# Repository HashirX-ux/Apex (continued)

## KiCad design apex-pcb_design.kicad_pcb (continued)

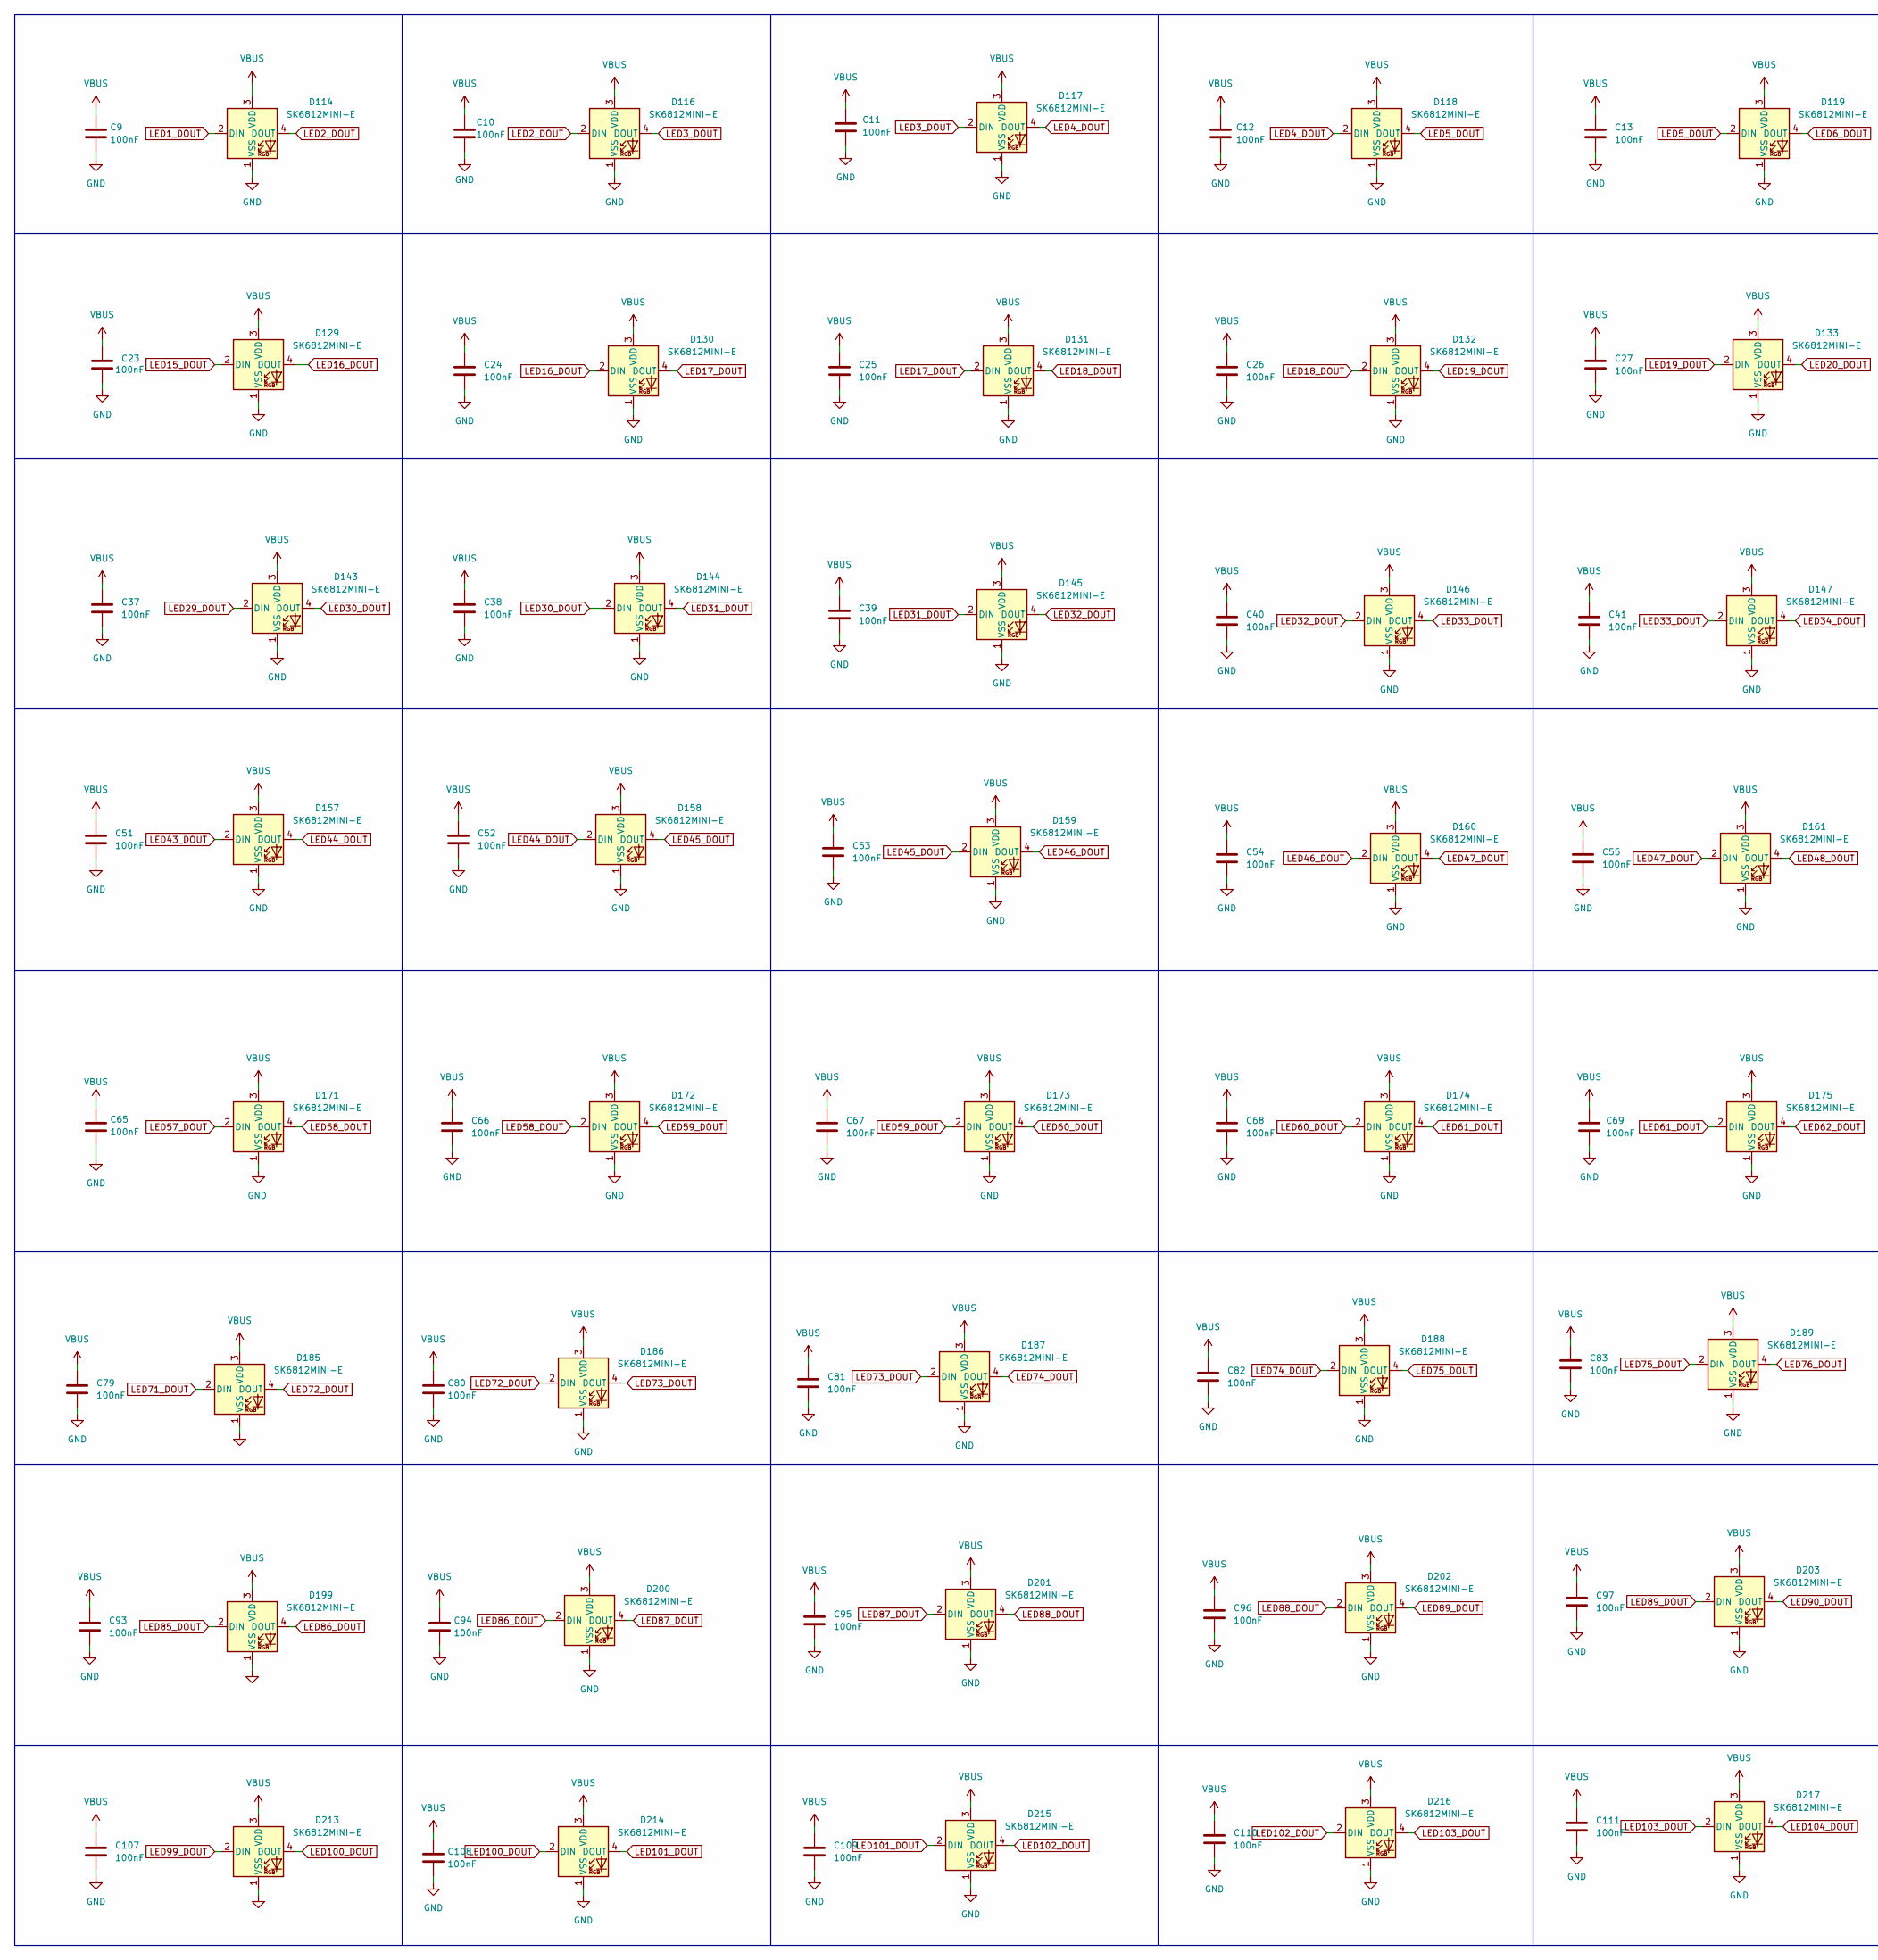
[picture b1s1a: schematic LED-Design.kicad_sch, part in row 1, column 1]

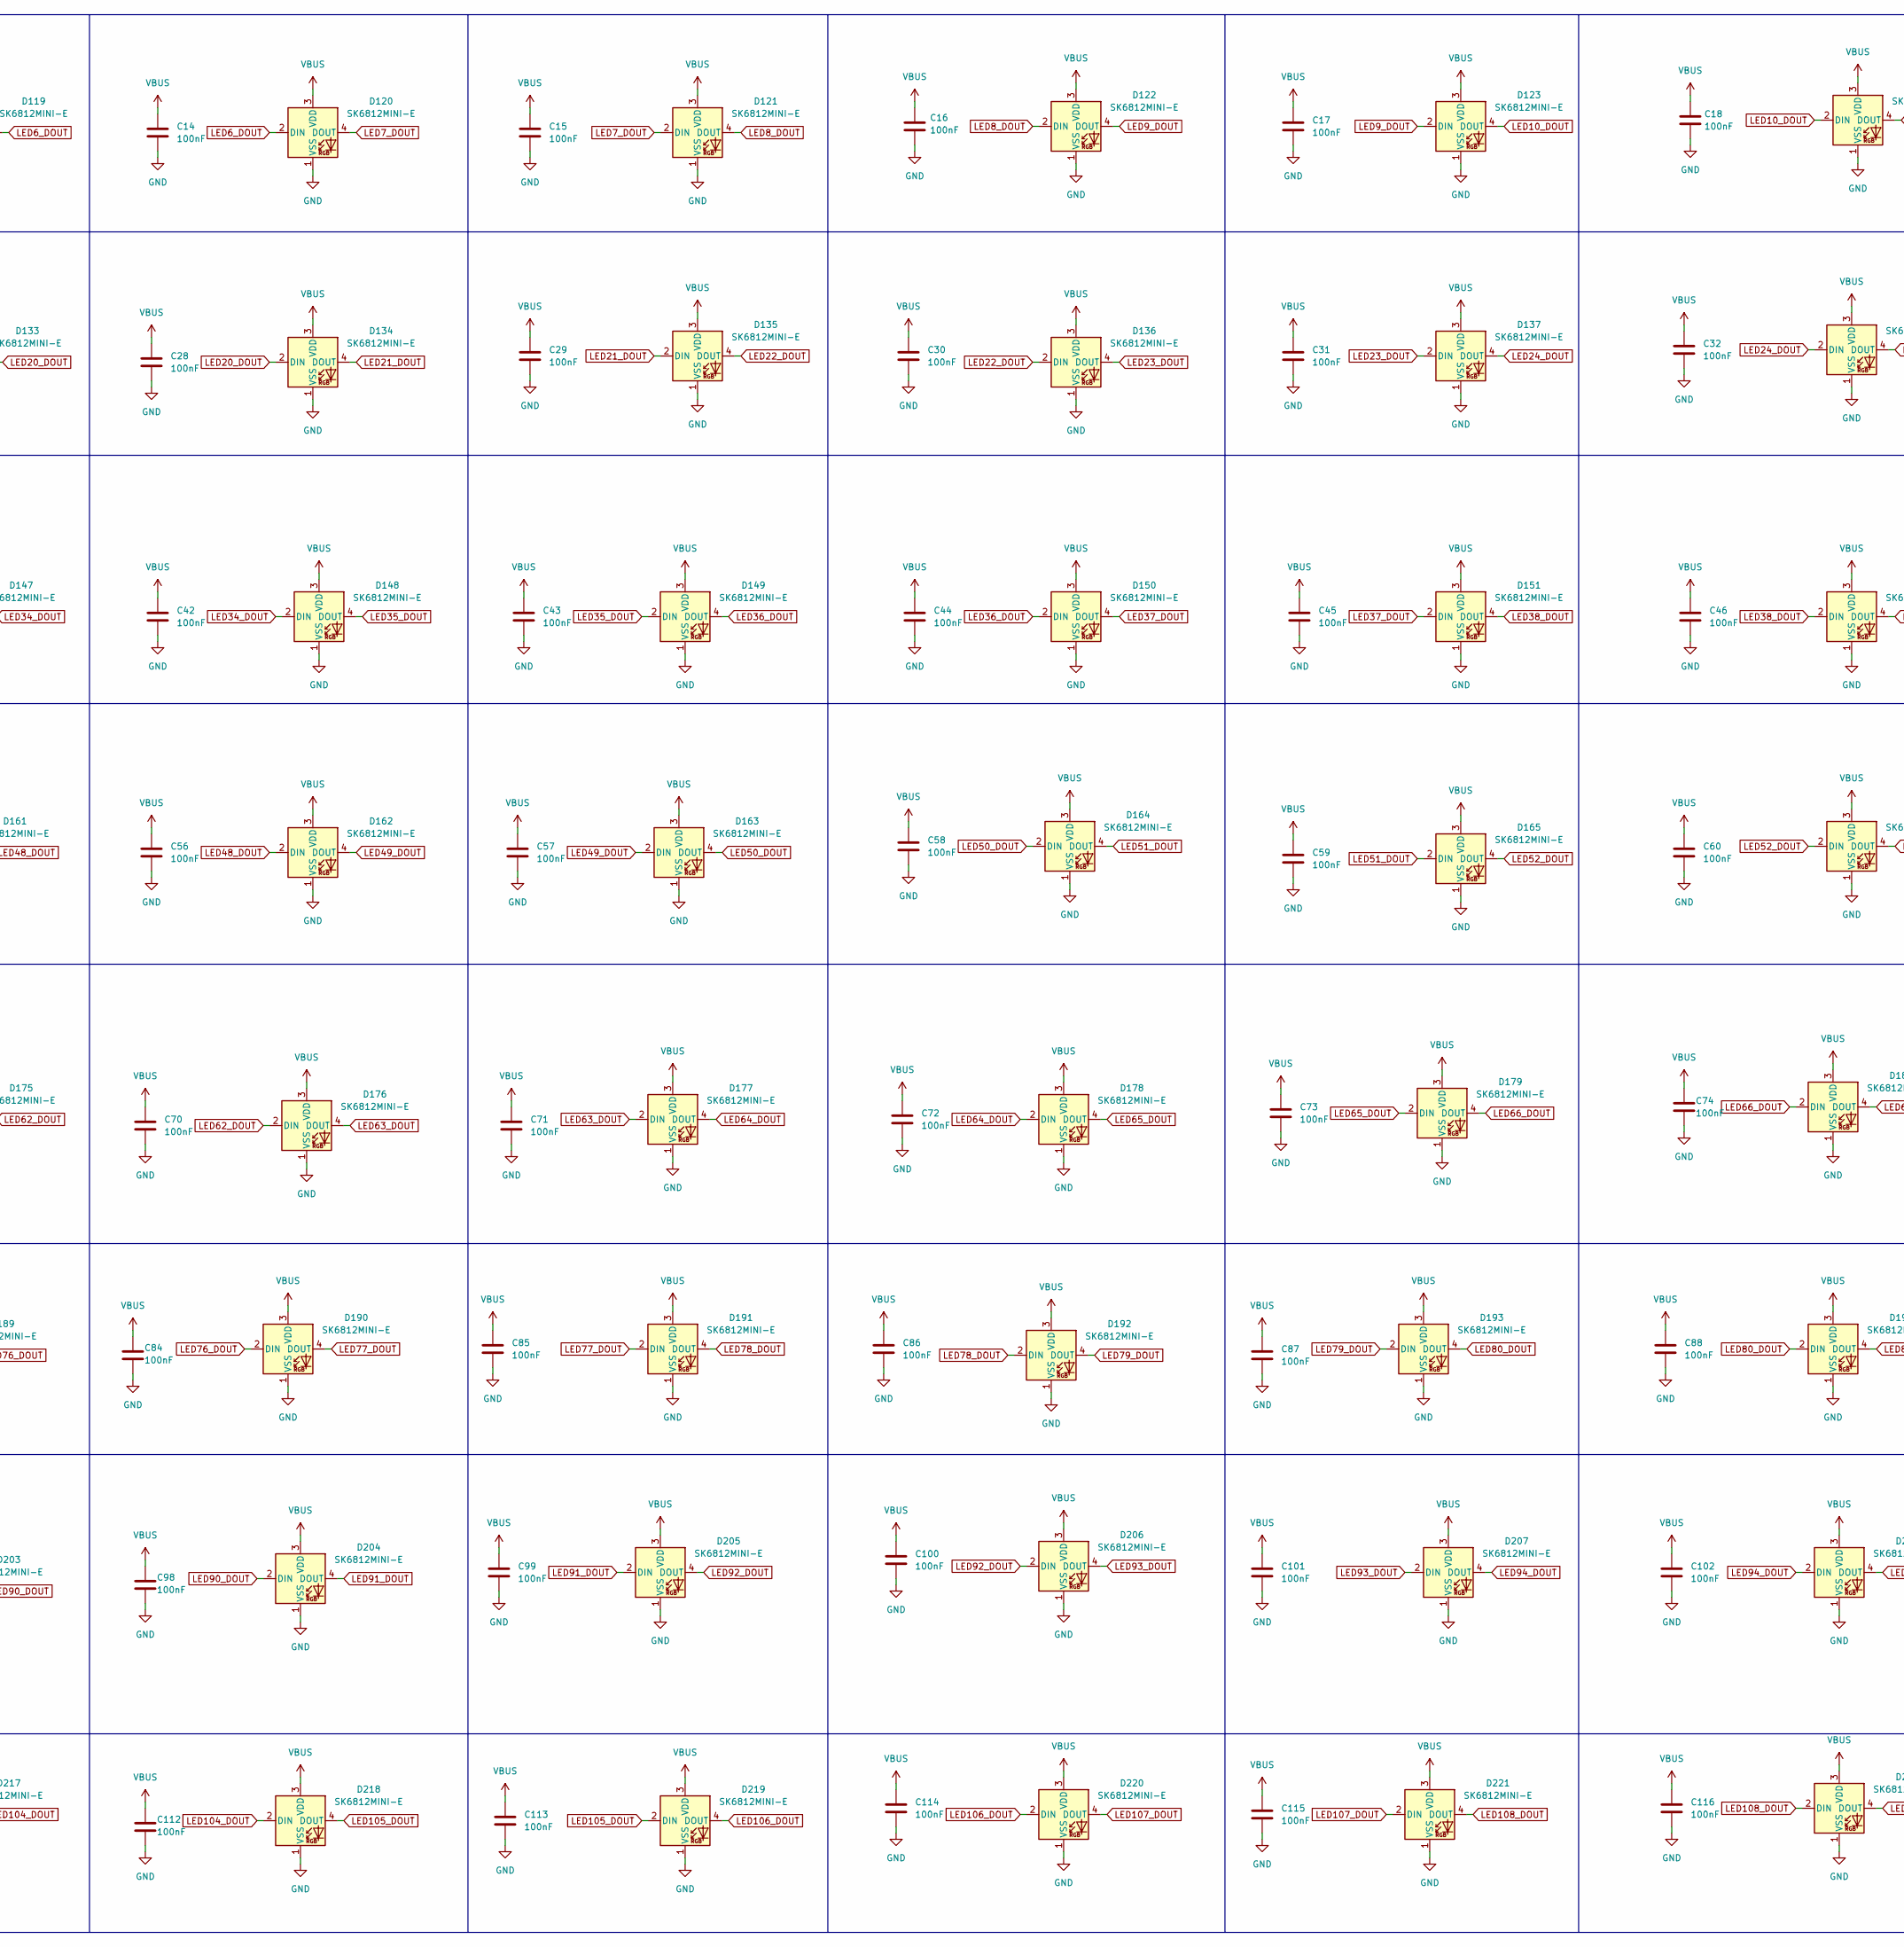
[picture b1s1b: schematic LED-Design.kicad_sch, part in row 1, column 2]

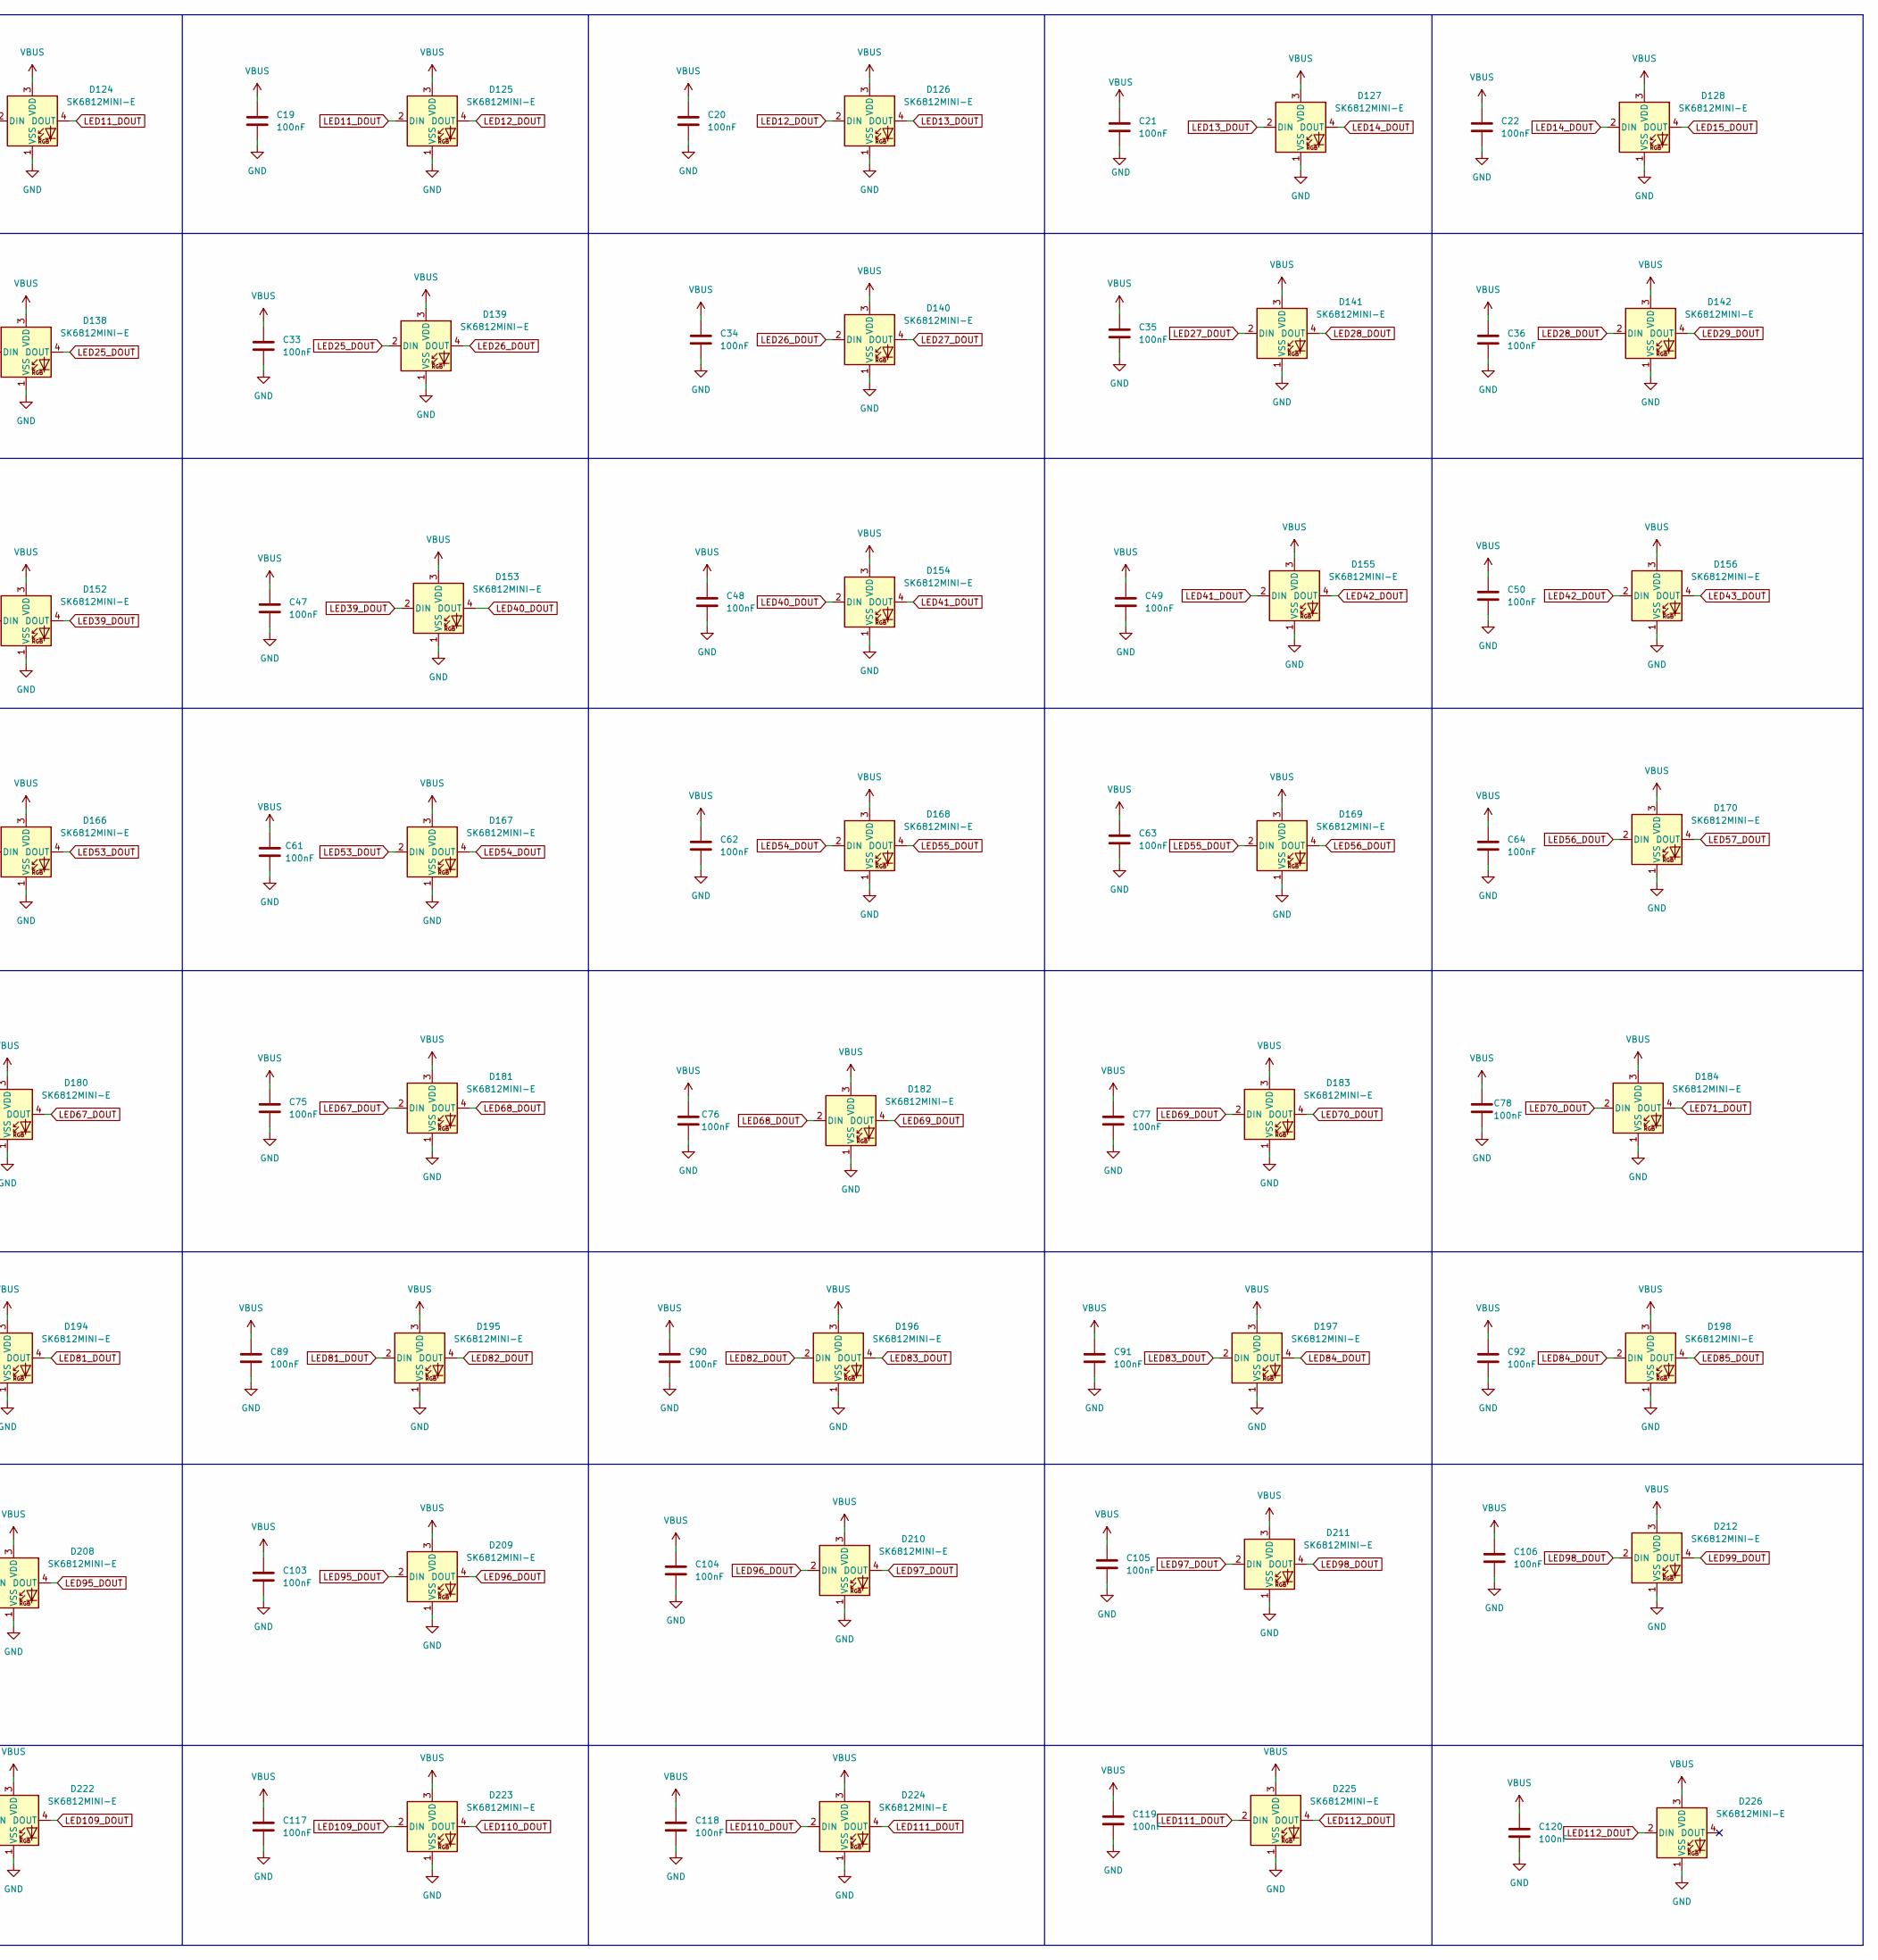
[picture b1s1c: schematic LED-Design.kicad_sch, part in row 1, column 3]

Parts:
C9, C10, C11, C12, C13, C14, C15, C16, C17, C18, C19, C20, C21, C22, C23, C24, C25, C26, C27, C28, C29, C30, C31, C32, C33, C34, C35, C36, C37, C38, C39, C40, C41, C42, C43, C44, C45, C46, C47, C48, C49, C50, C51, C52, C53, C54, C55, C56, C57, C58, C59, C60, C61, C62, C63, C64, C65, C66, C67, C68, C69, C70, C71, C72, C73, C74, C75, C76, C77, C78, C79, C80, C81, C82, C83, C84, C85, C86, C87, C88, C89, C90, C91, C92, C93, C94, C95, C96, C97, C98, C99, C100, C101, C102, C103, C104, C105, C106, C107, C108, C109, C110, C111, C112, C113, C114, C115, C116, C117, C118, C119, C120: 100nF; C_0805_2012Metric_Pad1.18x1.45mm_HandSolder
D114, D116, D117, D118, D119, D120, D121, D122, D123, D124, D125, D126, D127, D128, D129, D130, D131, D132, D133, D134, D135, D136, D137, D138, D139, D140, D141, D142, D143, D144, D145, D146, D147, D148, D149, D150, D151, D152, D153, D154, D155, D156, D157, D158, D159, D160, D161, D162, D163, D164, D165, D166, D167, D168, D169, D170, D171, D172, D173, D174, D175, D176, D177, D178, D179, D180, D181, D182, D183, D184, D185, D186, D187, D188, D189, D190, D191, D192, D193, D194, D195, D196, D197, D198, D199, D200, D201, D202, D203, D204, D205, D206, D207, D208, D209, D210, D211, D212, D213, D214, D215, D216, D217, D218, D219, D220, D221, D222, D223, D224, D225, D226: SK6812MINI-E; LED_SK6812MINI-E_3.2x2.8mm_P1.5mm_ReverseMount

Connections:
GND: C9.2, C10.2, C11.2, C12.2, C13.2, C14.2, C15.2, C16.2, C17.2, C18.2, C19.2, C20.2, C21.2, C22.2, C23.2, C24.2, C25.2, C26.2, C27.2, C28.2, C29.2, C30.2, C31.2, C32.2, C33.2, C34.2, C35.2, C36.2, C37.2, C38.2, C39.2, C40.2, C41.2, C42.2, C43.2, C44.2, C45.2, C46.2, C47.2, C48.2, C49.2, C50.2, C51.2, C52.2, C53.2, C54.2, C55.2, C56.2, C57.2, C58.2, C59.2, C60.2, C61.2, C62.2, C63.2, C64.2, C65.2, C66.2, C67.2, C68.2, C69.2, C70.2, C71.2, C72.2, C73.2, C74.2, C75.2, C76.2, C77.2, C78.2, C79.2, C80.2, C81.2, C82.2, C83.2, C84.2, C85.2, C86.2, C87.2, C88.2, C89.2, C90.2, C91.2, C92.2, C93.2, C94.2, C95.2, C96.2, C97.2, C98.2, C99.2, C100.2, C101.2, C102.2, C103.2, C104.2, C105.2, C106.2, C107.2, C108.2, C109.2, C110.2, C111.2, C112.2, C113.2, C114.2, C115.2, C116.2, C117.2, C118.2, C119.2, C120.2, D114.1 (VSS), D116.1 (VSS), D117.1 (VSS), D118.1 (VSS), D119.1 (VSS), D120.1 (VSS), D121.1 (VSS), D122.1 (VSS), D123.1 (VSS), D124.1 (VSS), D125.1 (VSS), D126.1 (VSS), D127.1 (VSS), D128.1 (VSS), D129.1 (VSS), D130.1 (VSS), D131.1 (VSS), D132.1 (VSS), D133.1 (VSS), D134.1 (VSS), D135.1 (VSS), D136.1 (VSS), D137.1 (VSS), D138.1 (VSS), D139.1 (VSS), D140.1 (VSS), D141.1 (VSS), D142.1 (VSS), D143.1 (VSS), D144.1 (VSS), D145.1 (VSS), D146.1 (VSS), D147.1 (VSS), D148.1 (VSS), D149.1 (VSS), D150.1 (VSS), D151.1 (VSS), D152.1 (VSS), D153.1 (VSS), D154.1 (VSS), D155.1 (VSS), D156.1 (VSS), D157.1 (VSS), D158.1 (VSS), D159.1 (VSS), D160.1 (VSS), D161.1 (VSS), D162.1 (VSS), D163.1 (VSS), D164.1 (VSS), D165.1 (VSS), D166.1 (VSS), D167.1 (VSS), D168.1 (VSS), D169.1 (VSS), D170.1 (VSS), D171.1 (VSS), D172.1 (VSS), D173.1 (VSS), D174.1 (VSS), D175.1 (VSS), D176.1 (VSS), D177.1 (VSS), D178.1 (VSS), D179.1 (VSS), D180.1 (VSS), D181.1 (VSS), D182.1 (VSS), D183.1 (VSS), D184.1 (VSS), D185.1 (VSS), D186.1 (VSS), D187.1 (VSS), D188.1 (VSS), D189.1 (VSS), D190.1 (VSS), D191.1 (VSS), D192.1 (VSS), D193.1 (VSS), D194.1 (VSS), D195.1 (VSS), D196.1 (VSS), D197.1 (VSS), D198.1 (VSS), D199.1 (VSS), D200.1 (VSS), D201.1 (VSS), D202.1 (VSS), D203.1 (VSS), D204.1 (VSS), D205.1 (VSS), D206.1 (VSS), D207.1 (VSS), D208.1 (VSS), D209.1 (VSS), D210.1 (VSS), D211.1 (VSS), D212.1 (VSS), D213.1 (VSS), D214.1 (VSS), D215.1 (VSS), D216.1 (VSS), D217.1 (VSS), D218.1 (VSS), D219.1 (VSS), D220.1 (VSS), D221.1 (VSS), D222.1 (VSS), D223.1 (VSS), D224.1 (VSS), D225.1 (VSS), D226.1 (VSS); also elsewhere on the board
LED3_DOUT: D116.4 (DOUT), D117.2 (DIN)
LED4_DOUT: D117.4 (DOUT), D118.2 (DIN)
LED5_DOUT: D118.4 (DOUT), D119.2 (DIN)
LED6_DOUT: D119.4 (DOUT), D120.2 (DIN)
LED7_DOUT: D120.4 (DOUT), D121.2 (DIN)
LED8_DOUT: D121.4 (DOUT), D122.2 (DIN)
LED9_DOUT: D122.4 (DOUT), D123.2 (DIN)
LED10_DOUT: D123.4 (DOUT), D124.2 (DIN)
LED11_DOUT: D124.4 (DOUT), D125.2 (DIN)
LED12_DOUT: D125.4 (DOUT), D126.2 (DIN)
LED13_DOUT: D126.4 (DOUT), D127.2 (DIN)
LED14_DOUT: D127.4 (DOUT), D128.2 (DIN)
LED15_DOUT: D128.4 (DOUT), D129.2 (DIN)
LED16_DOUT: D129.4 (DOUT), D130.2 (DIN)
LED17_DOUT: D130.4 (DOUT), D131.2 (DIN)
LED18_DOUT: D131.4 (DOUT), D132.2 (DIN)
LED19_DOUT: D132.4 (DOUT), D133.2 (DIN)
LED20_DOUT: D133.4 (DOUT), D134.2 (DIN)
LED21_DOUT: D134.4 (DOUT), D135.2 (DIN)
LED22_DOUT: D135.4 (DOUT), D136.2 (DIN)
LED23_DOUT: D136.4 (DOUT), D137.2 (DIN)
LED24_DOUT: D137.4 (DOUT), D138.2 (DIN)
LED25_DOUT: D138.4 (DOUT), D139.2 (DIN)
LED26_DOUT: D139.4 (DOUT), D140.2 (DIN)
LED27_DOUT: D140.4 (DOUT), D141.2 (DIN)
LED28_DOUT: D141.4 (DOUT), D142.2 (DIN)
LED29_DOUT: D142.4 (DOUT), D143.2 (DIN)
LED30_DOUT: D143.4 (DOUT), D144.2 (DIN)
LED31_DOUT: D144.4 (DOUT), D145.2 (DIN)
LED32_DOUT: D145.4 (DOUT), D146.2 (DIN)
LED33_DOUT: D146.4 (DOUT), D147.2 (DIN)
LED34_DOUT: D147.4 (DOUT), D148.2 (DIN)
LED35_DOUT: D148.4 (DOUT), D149.2 (DIN)
LED36_DOUT: D149.4 (DOUT), D150.2 (DIN)
LED37_DOUT: D150.4 (DOUT), D151.2 (DIN)
LED38_DOUT: D151.4 (DOUT), D152.2 (DIN)
LED39_DOUT: D152.4 (DOUT), D153.2 (DIN)
LED40_DOUT: D153.4 (DOUT), D154.2 (DIN)
LED41_DOUT: D154.4 (DOUT), D155.2 (DIN)
LED42_DOUT: D155.4 (DOUT), D156.2 (DIN)
LED43_DOUT: D156.4 (DOUT), D157.2 (DIN)
LED44_DOUT: D157.4 (DOUT), D158.2 (DIN)
LED45_DOUT: D158.4 (DOUT), D159.2 (DIN)
LED46_DOUT: D159.4 (DOUT), D160.2 (DIN)
LED47_DOUT: D160.4 (DOUT), D161.2 (DIN)
LED48_DOUT: D161.4 (DOUT), D162.2 (DIN)
LED49_DOUT: D162.4 (DOUT), D163.2 (DIN)
LED50_DOUT: D163.4 (DOUT), D164.2 (DIN)
LED51_DOUT: D164.4 (DOUT), D165.2 (DIN)
LED52_DOUT: D165.4 (DOUT), D166.2 (DIN)
LED53_DOUT: D166.4 (DOUT), D167.2 (DIN)
LED54_DOUT: D167.4 (DOUT), D168.2 (DIN)
LED55_DOUT: D168.4 (DOUT), D169.2 (DIN)
LED56_DOUT: D169.4 (DOUT), D170.2 (DIN)
LED57_DOUT: D170.4 (DOUT), D171.2 (DIN)
LED58_DOUT: D171.4 (DOUT), D172.2 (DIN)
LED59_DOUT: D172.4 (DOUT), D173.2 (DIN)
LED60_DOUT: D173.4 (DOUT), D174.2 (DIN)
LED61_DOUT: D174.4 (DOUT), D175.2 (DIN)
LED62_DOUT: D175.4 (DOUT), D176.2 (DIN)
LED63_DOUT: D176.4 (DOUT), D177.2 (DIN)
LED64_DOUT: D177.4 (DOUT), D178.2 (DIN)
LED65_DOUT: D178.4 (DOUT), D179.2 (DIN)
LED66_DOUT: D179.4 (DOUT), D180.2 (DIN)
LED67_DOUT: D180.4 (DOUT), D181.2 (DIN)
LED68_DOUT: D181.4 (DOUT), D182.2 (DIN)
LED69_DOUT: D182.4 (DOUT), D183.2 (DIN)
LED70_DOUT: D183.4 (DOUT), D184.2 (DIN)
LED71_DOUT: D184.4 (DOUT), D185.2 (DIN)
LED72_DOUT: D185.4 (DOUT), D186.2 (DIN)
LED73_DOUT: D186.4 (DOUT), D187.2 (DIN)
LED74_DOUT: D187.4 (DOUT), D188.2 (DIN)
LED75_DOUT: D188.4 (DOUT), D189.2 (DIN)
LED76_DOUT: D189.4 (DOUT), D190.2 (DIN)
LED77_DOUT: D190.4 (DOUT), D191.2 (DIN)
LED78_DOUT: D191.4 (DOUT), D192.2 (DIN)
LED79_DOUT: D192.4 (DOUT), D193.2 (DIN)
LED80_DOUT: D193.4 (DOUT), D194.2 (DIN)
LED81_DOUT: D194.4 (DOUT), D195.2 (DIN)
LED82_DOUT: D195.4 (DOUT), D196.2 (DIN)
LED83_DOUT: D196.4 (DOUT), D197.2 (DIN)
LED84_DOUT: D197.4 (DOUT), D198.2 (DIN)
LED85_DOUT: D198.4 (DOUT), D199.2 (DIN)
LED86_DOUT: D199.4 (DOUT), D200.2 (DIN)
LED87_DOUT: D200.4 (DOUT), D201.2 (DIN)
LED88_DOUT: D201.4 (DOUT), D202.2 (DIN)
LED89_DOUT: D202.4 (DOUT), D203.2 (DIN)
LED90_DOUT: D203.4 (DOUT), D204.2 (DIN)
LED91_DOUT: D204.4 (DOUT), D205.2 (DIN)
LED92_DOUT: D205.4 (DOUT), D206.2 (DIN)
LED93_DOUT: D206.4 (DOUT), D207.2 (DIN)
LED94_DOUT: D207.4 (DOUT), D208.2 (DIN)
LED95_DOUT: D208.4 (DOUT), D209.2 (DIN)
LED96_DOUT: D209.4 (DOUT), D210.2 (DIN)
LED97_DOUT: D210.4 (DOUT), D211.2 (DIN)
LED98_DOUT: D211.4 (DOUT), D212.2 (DIN)
LED99_DOUT: D212.4 (DOUT), D213.2 (DIN)
LED100_DOUT: D213.4 (DOUT), D214.2 (DIN)
LED101_DOUT: D214.4 (DOUT), D215.2 (DIN)
LED102_DOUT: D215.4 (DOUT), D216.2 (DIN)
LED103_DOUT: D216.4 (DOUT), D217.2 (DIN)
LED104_DOUT: D217.4 (DOUT), D218.2 (DIN)
LED105_DOUT: D218.4 (DOUT), D219.2 (DIN)
LED106_DOUT: D219.4 (DOUT), D220.2 (DIN)
LED107_DOUT: D220.4 (DOUT), D221.2 (DIN)
LED108_DOUT: D221.4 (DOUT), D222.2 (DIN)
LED109_DOUT: D222.4 (DOUT), D223.2 (DIN)
LED110_DOUT: D223.4 (DOUT), D224.2 (DIN)
LED111_DOUT: D224.4 (DOUT), D225.2 (DIN)
LED112_DOUT: D225.4 (DOUT), D226.2 (DIN)
VBUS: C9.1, C10.1, C11.1, C12.1, C13.1, C14.1, C15.1, C16.1, C17.1, C18.1, C19.1, C20.1, C21.1, C22.1, C23.1, C24.1, C25.1, C26.1, C27.1, C28.1, C29.1, C30.1, C31.1, C32.1, C33.1, C34.1, C35.1, C36.1, C37.1, C38.1, C39.1, C40.1, C41.1, C42.1, C43.1, C44.1, C45.1, C46.1, C47.1, C48.1, C49.1, C50.1, C51.1, C52.1, C53.1, C54.1, C55.1, C56.1, C57.1, C58.1, C59.1, C60.1, C61.1, C62.1, C63.1, C64.1, C65.1, C66.1, C67.1, C68.1, C69.1, C70.1, C71.1, C72.1, C73.1, C74.1, C75.1, C76.1, C77.1, C78.1, C79.1, C80.1, C81.1, C82.1, C83.1, C84.1, C85.1, C86.1, C87.1, C88.1, C89.1, C90.1, C91.1, C92.1, C93.1, C94.1, C95.1, C96.1, C97.1, C98.1, C99.1, C100.1, C101.1, C102.1, C103.1, C104.1, C105.1, C106.1, C107.1, C108.1, C109.1, C110.1, C111.1, C112.1, C113.1, C114.1, C115.1, C116.1, C117.1, C118.1, C119.1, C120.1, D114.3 (VDD), D116.3 (VDD), D117.3 (VDD), D118.3 (VDD), D119.3 (VDD), D120.3 (VDD), D121.3 (VDD), D122.3 (VDD), D123.3 (VDD), D124.3 (VDD), D125.3 (VDD), D126.3 (VDD), D127.3 (VDD), D128.3 (VDD), D129.3 (VDD), D130.3 (VDD), D131.3 (VDD), D132.3 (VDD), D133.3 (VDD), D134.3 (VDD), D135.3 (VDD), D136.3 (VDD), D137.3 (VDD), D138.3 (VDD), D139.3 (VDD), D140.3 (VDD), D141.3 (VDD), D142.3 (VDD), D143.3 (VDD), D144.3 (VDD), D145.3 (VDD), D146.3 (VDD), D147.3 (VDD), D148.3 (VDD), D149.3 (VDD), D150.3 (VDD), D151.3 (VDD), D152.3 (VDD), D153.3 (VDD), D154.3 (VDD), D155.3 (VDD), D156.3 (VDD), D157.3 (VDD), D158.3 (VDD), D159.3 (VDD), D160.3 (VDD), D161.3 (VDD), D162.3 (VDD), D163.3 (VDD), D164.3 (VDD), D165.3 (VDD), D166.3 (VDD), D167.3 (VDD), D168.3 (VDD), D169.3 (VDD), D170.3 (VDD), D171.3 (VDD), D172.3 (VDD), D173.3 (VDD), D174.3 (VDD), D175.3 (VDD), D176.3 (VDD), D177.3 (VDD), D178.3 (VDD), D179.3 (VDD), D180.3 (VDD), D181.3 (VDD), D182.3 (VDD), D183.3 (VDD), D184.3 (VDD), D185.3 (VDD), D186.3 (VDD), D187.3 (VDD), D188.3 (VDD), D189.3 (VDD), D190.3 (VDD), D191.3 (VDD), D192.3 (VDD), D193.3 (VDD), D194.3 (VDD), D195.3 (VDD), D196.3 (VDD), D197.3 (VDD), D198.3 (VDD), D199.3 (VDD), D200.3 (VDD), D201.3 (VDD), D202.3 (VDD), D203.3 (VDD), D204.3 (VDD), D205.3 (VDD), D206.3 (VDD), D207.3 (VDD), D208.3 (VDD), D209.3 (VDD), D210.3 (VDD), D211.3 (VDD), D212.3 (VDD), D213.3 (VDD), D214.3 (VDD), D215.3 (VDD), D216.3 (VDD), D217.3 (VDD), D218.3 (VDD), D219.3 (VDD), D220.3 (VDD), D221.3 (VDD), D222.3 (VDD), D223.3 (VDD), D224.3 (VDD), D225.3 (VDD), D226.3 (VDD); also elsewhere on the board

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
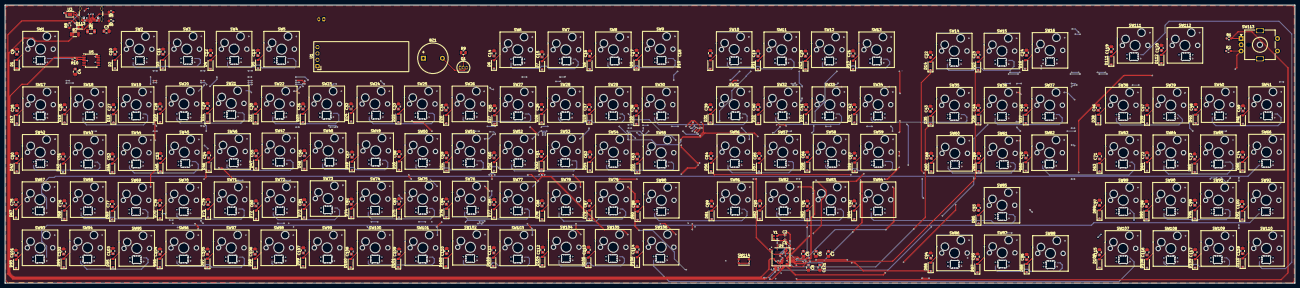
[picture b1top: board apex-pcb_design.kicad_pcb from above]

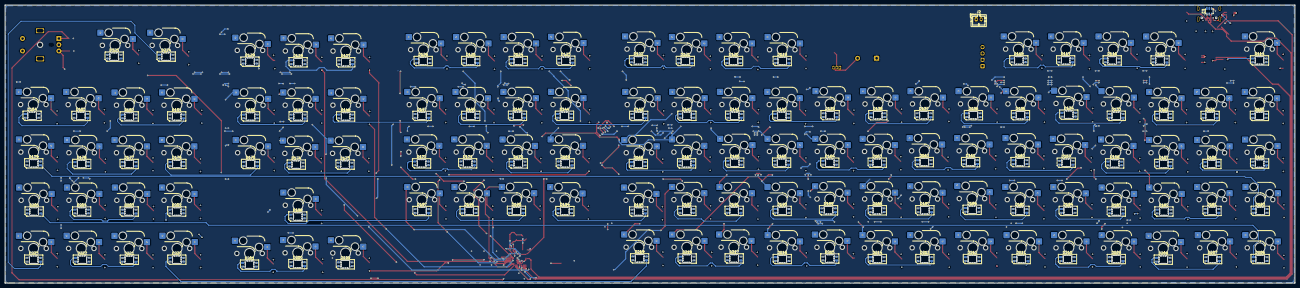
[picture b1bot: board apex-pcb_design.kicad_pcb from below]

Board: 4 copper layers, 515.5 x 111.1 mm, 479 parts (114 on the bottom side), 269 nets.
